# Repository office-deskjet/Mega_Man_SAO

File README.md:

# Mega_Man_SAO
Mega Man SAO 1.69

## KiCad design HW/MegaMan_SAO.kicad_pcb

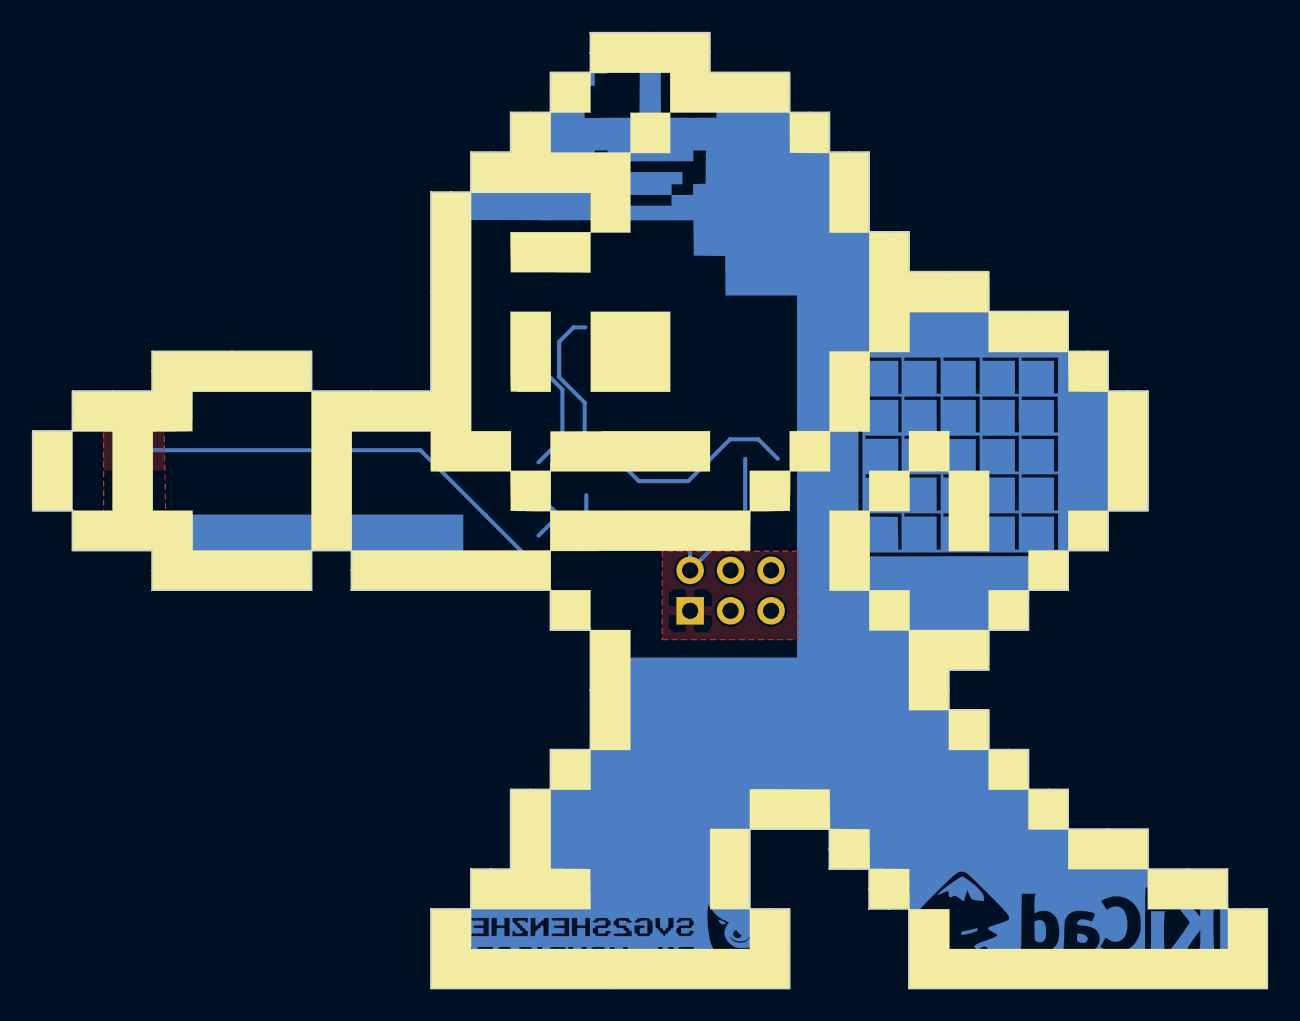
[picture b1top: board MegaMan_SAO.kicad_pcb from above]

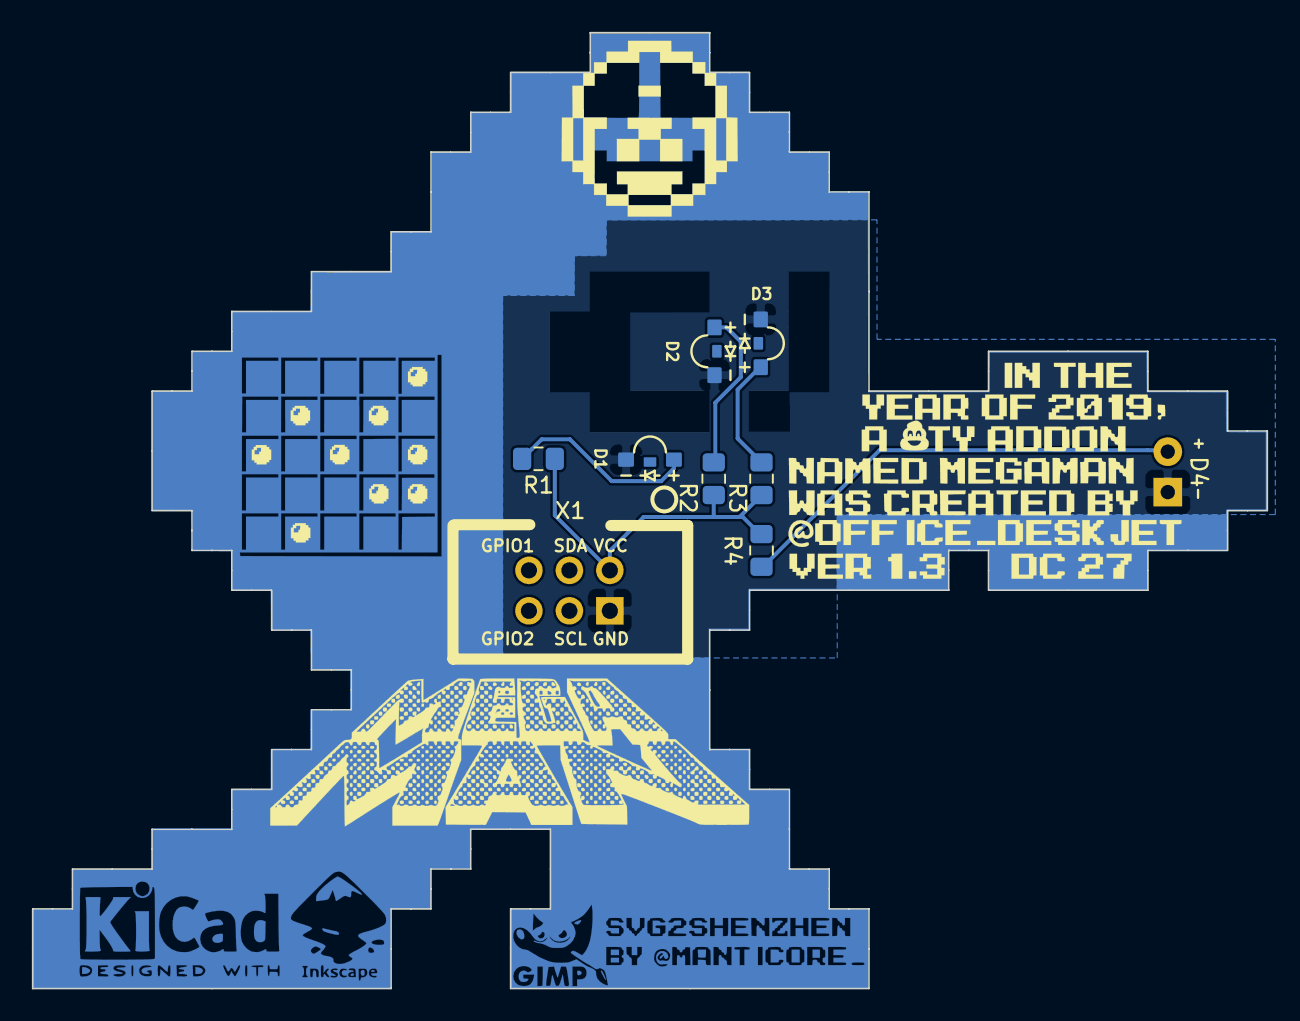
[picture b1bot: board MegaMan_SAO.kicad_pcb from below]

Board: 2 copper layers, 77.5 x 60.0 mm, 10 parts (7 on the bottom side), 6 nets.

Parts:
B.Cu: LOGO; B.Cu_g4148
D1, D2, D3: WHT_LED; 1204_SIDE_VIEW_LED
D4: YLW_LED; LED_D5.0mm_Horizontal_O6.35mm_Z3.0mm
R1, R2, R3: 50R; R_0805_2012Metric_Pad1.15x1.40mm_HandSolder
R4: 100R; R_0805_2012Metric_Pad1.15x1.40mm_HandSolder
X1: Badgelife_sao_connector_v169bis; Badgelife-SAOv169-SAO-2x3

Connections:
GND: D1.1, D2.1, D3.1, D4.1, X1.2
unnamed: D1.2, R1.2
unnamed: D2.2, R2.2
unnamed: D3.2, R3.2
unnamed: D4.2, R4.2
VCC: R1.1, R2.1, R3.1, R4.1, X1.1

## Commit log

2019-05-22 first
2019-05-22 ignore and art link
2019-05-22 fixed readme
2019-06-13 starting on art
2019-06-13 Initial art is done
2019-06-13 New KiCad project with art footprint
2019-06-14 Added footprints and library for LEDs and header
2019-06-14 placing parts
2019-06-14 Added B.cu Keep out, B.Cu ground pour
2019-06-14 added traces, fixed up ground pour
2019-06-14 Netlist, B.Silk Art, lib files
2019-07-02 art resources
2019-07-04 1up head art
2019-07-04 added 1UP art to back of board
2019-07-07 lots of art work changes
2019-07-07 Kicad foot print editor saves to PCB not footprint. have to manaully overwrite.
2019-07-19 Added Gerbers fixed the blaster LED anode short to ground on F.Cu
2019-07-19 remove unused footprints
2019-07-19 fixed the B.Mask on the password dots
2019-07-19 cleaned up B.Silk Text. Removed LEDs from schematic.
2019-07-19 Fixed ground in schematic and made new netlist. Working on layout
